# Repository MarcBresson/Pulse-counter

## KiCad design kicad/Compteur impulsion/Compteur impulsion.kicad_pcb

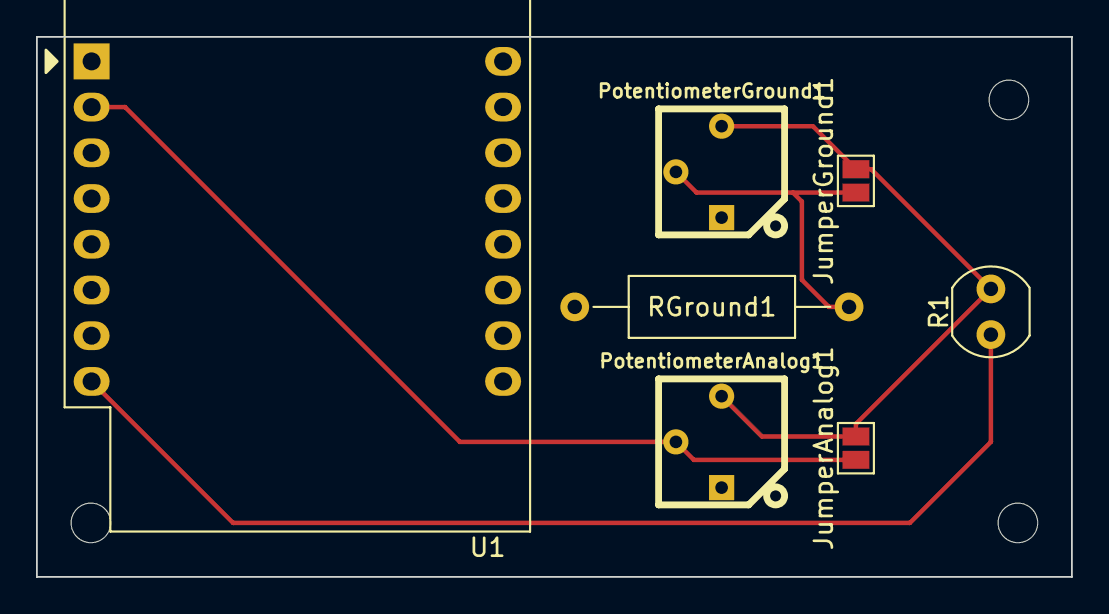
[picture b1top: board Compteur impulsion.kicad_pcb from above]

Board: 2 copper layers, 57.5 x 30.0 mm, 7 parts (0 on the bottom side), 4 nets.

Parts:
JumperAnalog1: SolderJumper_2_Open; SolderJumper-2_P1.3mm_Open_Pad1.0x1.5mm
JumperGround1: SolderJumper_2_Open; SolderJumper-2_P1.3mm_Open_Pad1.0x1.5mm
PotentiometerAnalog1: R_Potentiometer; BOURNS-3362P_pot
PotentiometerGround1: R_Potentiometer; BOURNS-3362P_pot
R1: R_Photo; R_LDR_4.9x4.2mm_P2.54mm_Vertical
RGround1: 500Ω; R_Axial_DIN0309_L9.0mm_D3.2mm_P15.24mm_Horizontal
U1: WeMos_D1_mini; WEMOS_D1_mini_light

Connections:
+3V3: R1.1, U1.8 (3V3)
A0: JumperAnalog1.1 (A), PotentiometerAnalog1.2, U1.2 (A0)
unnamed: JumperGround1.1 (A), PotentiometerGround1.2, RGround1.2
R_photo: JumperAnalog1.2 (B), JumperGround1.2 (B), PotentiometerAnalog1.3, PotentiometerGround1.3, R1.2
